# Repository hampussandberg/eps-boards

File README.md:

# ESP boards
Various ESP8266 and ESP32 boards

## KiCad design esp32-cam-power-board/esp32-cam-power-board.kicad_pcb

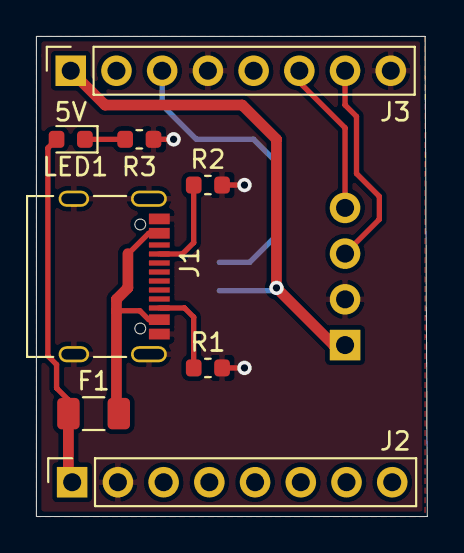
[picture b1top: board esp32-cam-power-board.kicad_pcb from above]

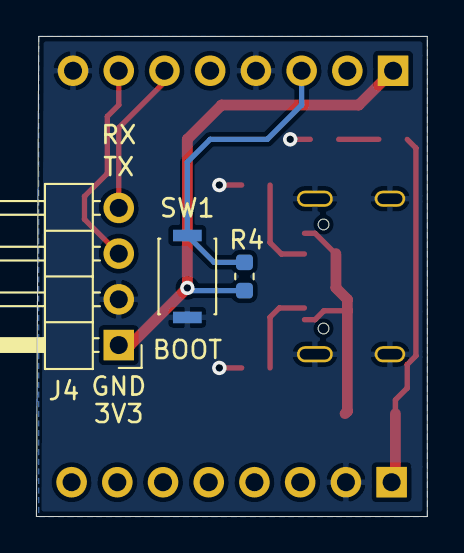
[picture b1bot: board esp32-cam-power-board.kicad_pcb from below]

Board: 2 copper layers, 21.7 x 26.7 mm, 11 parts (3 on the bottom side), 10 nets.

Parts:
F1: 0ZCJ0100FF2E; Fuse_1206_3216Metric
J1: USB_C_Receptacle_USB2.0; USB_C_Receptacle_Palconn_UTC16-G
J2, J3: Conn_01x08_Female; PinSocket_1x08_P2.54mm_Vertical
J4: Conn_01x04_Male; PinHeader_1x04_P2.54mm_Horizontal
LED1: Green; LED_0603_1608Metric
R1, R2: 5k1; R_0603_1608Metric
R3: 4k7; R_0603_1608Metric
R4: 10k; R_0603_1608Metric
SW1: SW_Push; SW_SPST_4x3x2mm

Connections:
+3V3: J3.1, J4.1, R4.1
/CC1: J1.A5, R2.1
/CC2: J1.B5, R1.1
/PP_VUSB: F1.1, J2.1, LED1.2
/PP_VUSB_RAW: F1.2, J1.A4, J1.A9, J1.B4, J1.B9
/RX: J3.6, J4.4
/TX: J3.7, J4.3
/~BOOT~: J3.3, R4.2, SW1.2
GND: J1.A1, J1.A12, J1.B1, J1.B12, J1.S1, J2.2, J3.4, J3.8, J4.2, R1.2, R2.2, R3.2, SW1.1
unnamed: LED1.1, R3.1

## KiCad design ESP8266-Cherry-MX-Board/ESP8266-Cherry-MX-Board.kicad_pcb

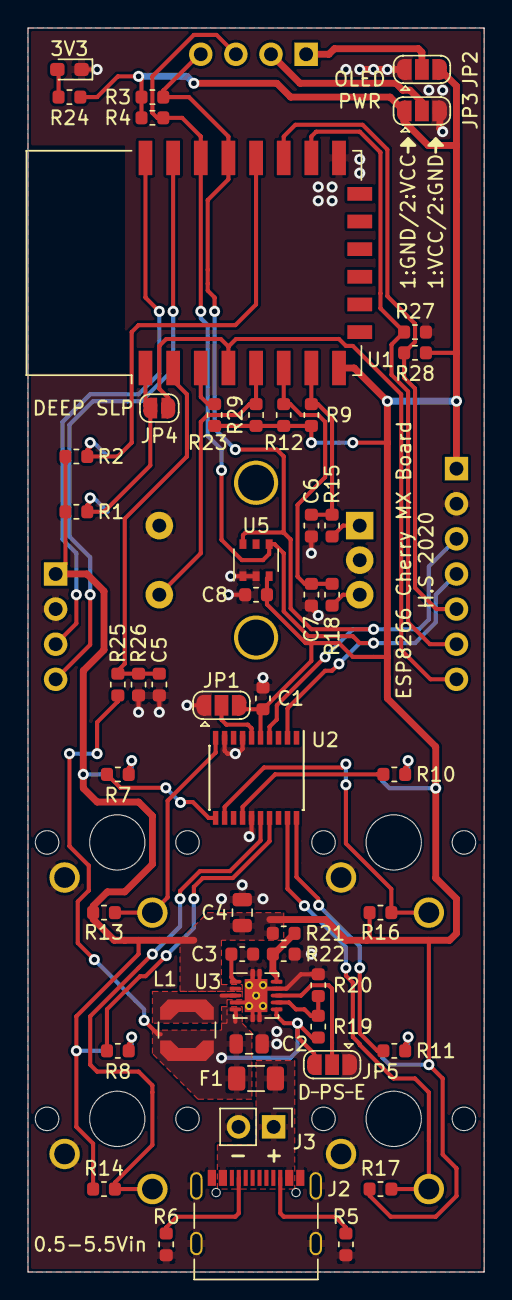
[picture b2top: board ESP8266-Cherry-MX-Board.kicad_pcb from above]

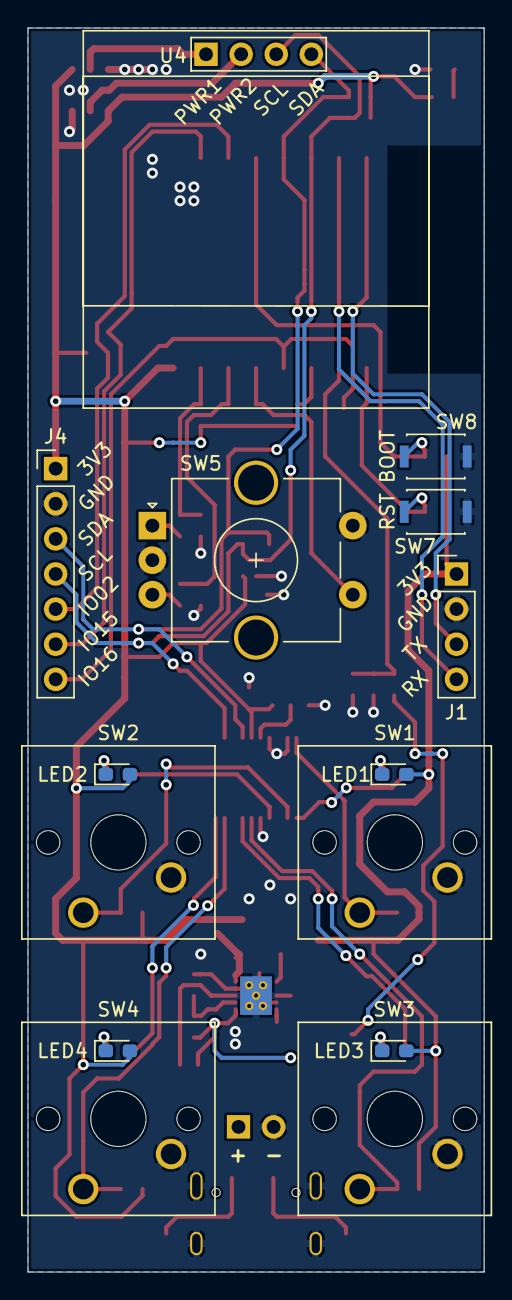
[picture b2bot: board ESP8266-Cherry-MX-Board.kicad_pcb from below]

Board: 2 copper layers, 33.0 x 90.0 mm, 65 parts (14 on the bottom side), 43 nets.

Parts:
3V3: Red; LED_0603_1608Metric_Pad1.05x0.95mm_HandSolder
C1, C3, C5, C8: 100n; C_0603_1608Metric
C2, C4: 10uF; C_0805_2012Metric
C6, C7: 10n; C_0603_1608Metric
F1: Polyfuse; Fuse_1206_3216Metric
J1: Conn_01x04_Male; PinHeader_1x04_P2.54mm_Vertical
J2: USB_C_Receptacle_USB2.0; USB_C_Receptacle_Palconn_UTC16-G
J3: Conn_01x02; PinHeader_1x02_P2.54mm_Vertical
J4: Conn_01x07_Male; PinHeader_1x07_P2.54mm_Vertical
JP1, JP2, JP3, JP5: SolderJumper_3_Open; SolderJumper-3_P1.3mm_Open_RoundedPad1.0x1.5mm
JP4: SolderJumper_2_Open; SolderJumper-2_P1.3mm_Open_RoundedPad1.0x1.5mm
L1: 2.2uH; L_Coilcraft_LPS4012
LED1, LED2, LED3, LED4: Blue; LED_0603_1608Metric_Pad1.05x0.95mm_HandSolder
R1, R2, R3, R4, R9, R12, R13, R14, R16, R17, R23, R24, R27, R28, R29: 10k; R_0603_1608Metric
R5, R6: 5.1k; R_0603_1608Metric
R7, R8, R10, R11: 330R; R_0603_1608Metric
R15, R18: 0R; R_0603_1608Metric
R19, R20, R22: 178k; R_0603_1608Metric
R21: 1M; R_0603_1608Metric
R25: 499k; R_0603_1608Metric
R26: 100k; R_0603_1608Metric
SW1, SW2, SW3, SW4: SW_SPST; SW_Cherry_MX_1.00u_PCB
SW5: PEC11L-4115F-S0020; RotaryEncoder_Alps_EC11E-Switch_Vertical_H20mm_CircularMoun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
SW7, SW8: SW_Push; SW_SPST_4x3x2mm
U1: ESP-12F; ESP-12E
U2: PCF8574; SSOP-20_4.4x6.5mm_P0.65mm
U3: TPS61200DRC; Texas_S-PVSON-N10_ThermalVias
U4: SSD1306; 128x64OLED
U5: PCT2075GVX‎; TSOP-6_1.65x3.05mm_P0.95mm

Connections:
+3V3: C1.2, C4.1, C8.2, J1.1, J4.1, JP1.3, JP2.3, JP3.1, LED1.2, LED2.2, LED3.2, LED4.2, R1.2, R2.2, R3.1, R4.1, R9.1, R12.1, R13.2, R14.2, R16.2, R17.2, R21.1, R23.1, R24.1, R28.1, R29.1, U1.8, U2.5, U3.2, U5.3
/ADC: C5.1, R25.1, R26.1, U1.2
/ENCODER_A: C6.1, R9.2, R15.1, U1.7
/ENCODER_B: C7.1, R12.2, R18.1, U1.6
/ENCODER_SW: R29.2, SW5.S1, U1.5
/GPIO0: R2.1, SW8.1, U1.18
/GPIO2: J4.5, R28.2, U1.17
/GPIO15: J4.6, R27.1, U1.16
/GPIO16: J4.7, JP4.2, U1.4
/I2C_SCL: J4.4, R4.2, U1.20, U2.2, U4.3, U5.4
/I2C_SDA: J4.3, R3.2, U1.19, U2.4, U4.4, U5.6
/LED_1: R7.1, U2.11
/LED_2: R10.1, U2.14
/LED_3: R8.1, U2.17
/LED_4: R11.1, U2.20
/RX: J1.4, U1.21
/SWITCH_1: R13.1, SW1.1, U2.10
/SWITCH_2: R16.1, SW2.1, U2.12
/SWITCH_3: R14.1, SW3.1, U2.16
/SWITCH_4: R17.1, SW4.1, U2.19
/TX: J1.3, U1.22
/~RST~: JP4.1, R1.1, SW7.2, U1.1
GND: 3V3.1, C1.1, C2.2, C3.2, C4.2, C5.2, C6.2, C7.2, C8.1, J1.2, J2.A1, J2.A12, J2.B1, J2.B12, J2.S1, J3.2, J4.2, JP1.1, JP2.1, JP3.3, JP5.1, R5.2, R6.2, R20.2, R22.2, R26.2, R27.2, SW1.2, SW2.2, SW3.2, SW4.2, SW5.C, SW5.S2, SW7.1, SW8.2, U1.15, U2.7, U2.9, U2.15, U3.4, U3.9, U3.11, U5.1, U5.2
unnamed: 3V3.2, R24.2
unnamed: C2.1, F1.1, JP5.3, L1.1, R19.1, R25.2, U3.5, U3.6
unnamed: C3.1, U3.1
unnamed: J2.A5, R6.1
unnamed: J2.B5, R5.1
unnamed: JP1.2, U2.6
unnamed: JP2.2, U4.1
unnamed: JP3.2, U4.2
unnamed: JP5.2, U3.8
unnamed: L1.2, U3.3
unnamed: LED1.1, R7.2
unnamed: LED2.1, R10.2
unnamed: LED3.1, R8.2
unnamed: LED4.1, R11.2
unnamed: R15.2, SW5.A
unnamed: R18.2, SW5.B
unnamed: R19.2, R20.1, U3.7
unnamed: R21.2, R22.1, U3.10
unnamed: R23.2, U1.3
VBUS: F1.2, J2.A4, J2.A9, J2.B4, J2.B9, J3.1

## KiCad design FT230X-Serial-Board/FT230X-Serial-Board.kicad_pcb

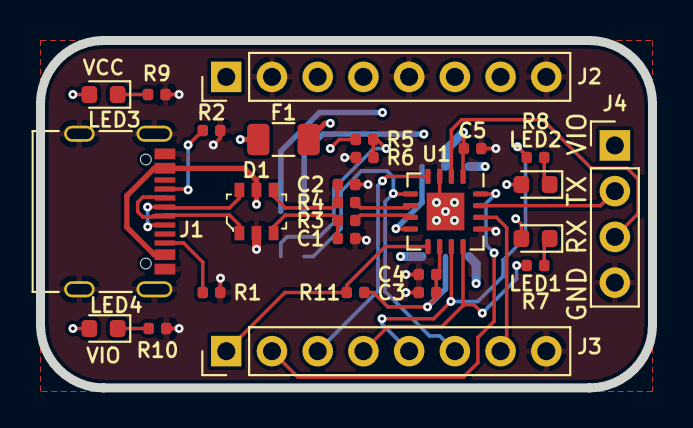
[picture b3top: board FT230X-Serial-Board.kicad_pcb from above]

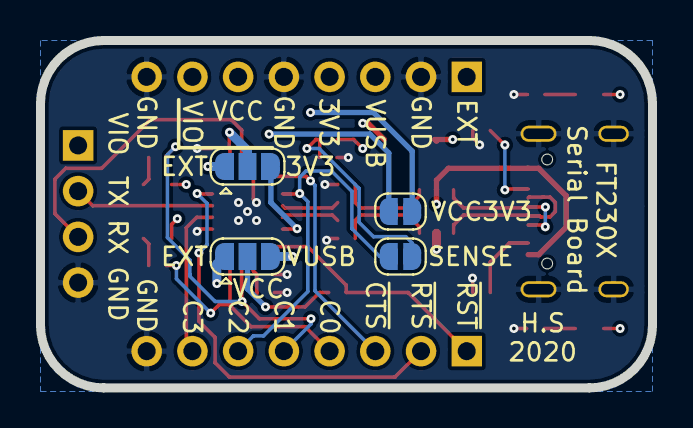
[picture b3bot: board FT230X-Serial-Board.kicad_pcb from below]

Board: 4 copper layers, 34.0 x 19.3 mm, 31 parts (4 on the bottom side), 29 nets.

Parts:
C1, C2: 47pF; C_0402_1005Metric
C3: 4u7; C_0402_1005Metric
C4, C5: 100n; C_0402_1005Metric
D1: IP4234CZ6; SC-74
F1: 0ZCJ0100FF2E; Fuse_1206_3216Metric
J1: USB_C_Receptacle_USB2.0; USB_C_Receptacle_Palconn_UTC16-G
J2, J3: Conn_01x08_Male; PinHeader_1x08_P2.54mm_Vertical
J4: Conn_01x04_Male; PinHeader_1x04_P2.54mm_Vertical
JP1, JP3: Jumper_3_Open; SolderJumper-3_P1.3mm_Open_RoundedPad1.0x1.5mm
JP2, JP4: Jumper_2_Open; SolderJumper-2_P1.3mm_Open_RoundedPad1.0x1.5mm
LED1: Red; LED_0603_1608Metric
LED2, LED3, LED4: Green; LED_0603_1608Metric
R1, R2: 5k1; R_0402_1005Metric
R3, R4: 27; R_0402_1005Metric
R5, R9, R10: 4k7; R_0402_1005Metric
R6: 10k; R_0402_1005Metric
R7, R8: 270; R_0402_1005Metric
R11: nc; R_0402_1005Metric
U1: FT230XQ; QFN-16-1EP_4x4mm_P0.65mm_EP2.1x2.1mm

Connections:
/CBUS0: J3.4, R7.2, U1.12
/CBUS1: J3.5, R8.2, U1.11
/CBUS2: J3.6, JP2.2, U1.5
/CBUS3: J3.7, U1.14
/CC1: J1.A5, R2.1
/CC2: J1.B5, R1.1
/PP3V3OUT: J2.4, JP3.3, JP4.2, U1.8
/PPEXT: J2.1, JP1.1, JP3.1
/PPIO: C5.2, J2.7, J4.1, JP3.2, LED1.2, LED2.2, LED4.2, U1.1
/PPVCC: C3.1, C4.2, J2.6, JP1.2, JP4.1, LED3.2, R11.1, U1.10
/PP_VUSB: F1.1, J2.3, JP1.3, R5.1
/PP_VUSB_RAW: D1.5, F1.2, J1.A4, J1.A9, J1.B4, J1.B9
/RESET_N: J3.1, R11.2, U1.9
/UART_RX: J4.3, U1.2
/UART_TX: J4.2, U1.15
/UART_~CTS: J3.3, U1.4
/UART_~RTS: J3.2, U1.16
/USBDR_N: R3.2, U1.7
/USBDR_P: R4.2, U1.6
/USB_D_N: C1.2, D1.3, R3.1
/USB_D_P: C2.2, D1.4, R4.1
/USB_D_RAW_N: D1.1, J1.A7, J1.B7
/USB_D_RAW_P: D1.6, J1.A6, J1.B6
/VUSB_SENSE: JP2.1, R5.2, R6.1
GND: C1.1, C2.1, C3.2, C4.1, C5.1, D1.2, J1.A1, J1.A12, J1.B1, J1.B12, J1.S1, J2.2, J2.5, J2.8, J3.8, J4.4, R1.2, R2.2, R6.2, R9.2, R10.2, U1.3, U1.13, U1.17
unnamed: LED1.1, R7.1
unnamed: LED2.1, R8.1
unnamed: LED3.1, R9.1
unnamed: LED4.1, R10.1

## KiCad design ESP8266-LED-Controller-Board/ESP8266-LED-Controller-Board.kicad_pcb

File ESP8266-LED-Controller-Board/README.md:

# ESP8266-LED-Controller-Board
- [GitHub repository <i class="fa fa-external-link"></i>](https://github.com/hampussandberg/esp-boards/tree/master/ESP8266-LED-Controller-Board)
- [Interactive BOM](ESP8266-LED-Controller-Board-ibom.html){target="\_blank"}

Interactive BOM created using: https://github.com/openscopeproject/InteractiveHtmlBom

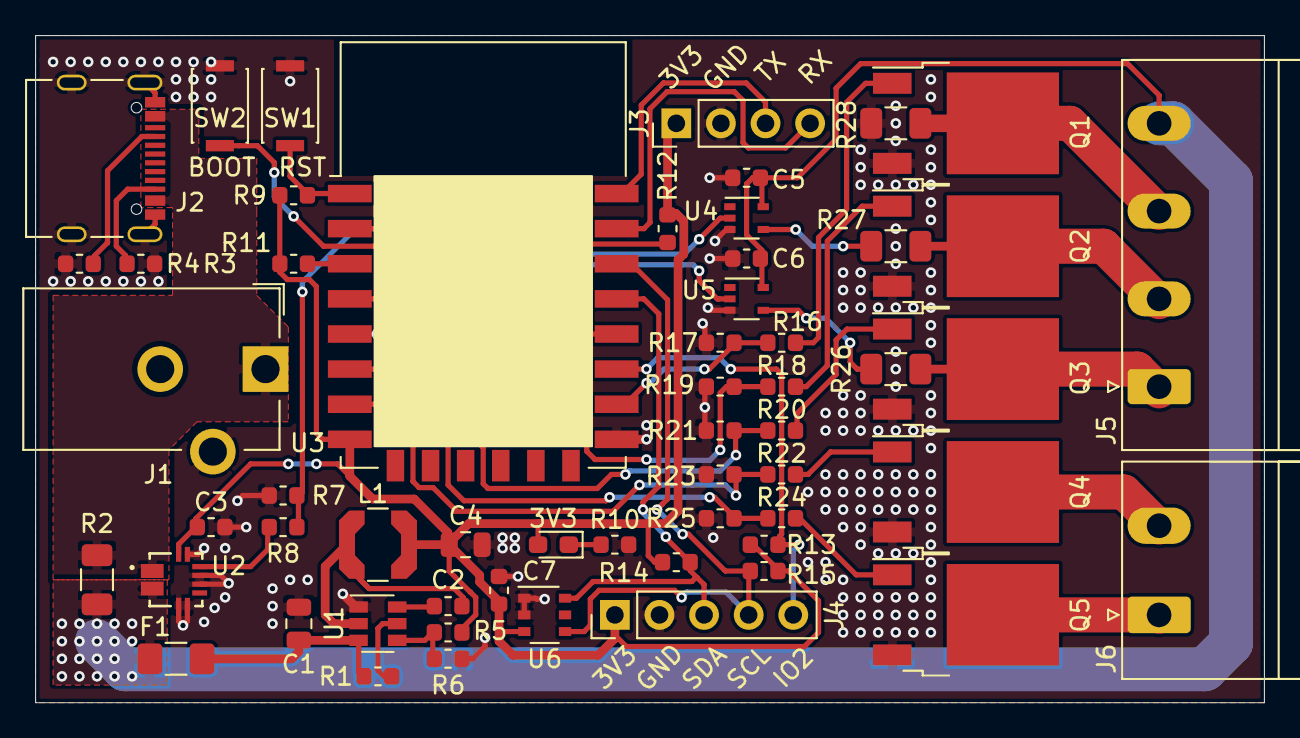
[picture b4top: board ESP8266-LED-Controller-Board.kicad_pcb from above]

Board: 2 copper layers, 70.0 x 38.0 mm, 57 parts (0 on the bottom side), 39 nets.

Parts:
3V3: RED; LED_0603_1608Metric_Pad1.05x0.95mm_HandSolder
C1, C4: 22u; C_0805_2012Metric
C2, C3, C5, C6, C7: 100n; C_0603_1608Metric
F1: 0ZCJ0050AF2E; Fuse_0ZCJ_1206
J1: Barrel_Jack_Switch; BarrelJack_CUI_PJ-102AH_Horizontal
J2: USB_C_Receptacle_USB2.0; USB_C_Receptacle_Palconn_UTC16-G
J3: Conn_01x04_Male; PinHeader_1x04_P2.54mm_Vertical
J4: Conn_01x05_Male; PinHeader_1x05_P2.54mm_Vertical
J5: Screw_Terminal_01x04; PhoenixContact_MSTBA_2,5_4-G_1x04_P5.00mm_Horizontal
J6: Screw_Terminal_01x02; PhoenixContact_MSTBA_2,5_2-G-5,08_1x02_P5.08mm_Horizontal
L1: 2.2uH; L_Coilcraft_LPS4012
Q1, Q2, Q3, Q4, Q5: NTD5867NLT4G; TO-252-2
R1, R6, R7, R9, R10, R11, R12, R13, R14, R15, R17, R19, R21, R23, R25: 10k; R_0603_1608Metric
R2, R26, R27, R28: 0R; R_1206_3216Metric
R3, R4: 5k1; R_0603_1608Metric
R5: 33k2; R_0603_1608Metric
R8: 22k; R_0603_1608Metric
R16, R18, R20, R22, R24: 100R; R_0603_1608Metric
SW1, SW2: SW_Push; SW_SPST_4x3x2mm
U1: TPS563200; SOT-23-6
U2: ACS70331EESATR-005U3; ALLEGRO_ACS70331EESATR-005U3
U3: ESP-12F; ESP-12E
U4, U5: SN74LV1T34DCKR; SOT-353_SC-70-5
U6: PCT2075GVX‎; TSOP-6_1.65x3.05mm_P0.95mm

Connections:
+3V3: 3V3.2, C3.1, C4.1, C7.2, J3.1, J4.1, L1.2, R5.1, R9.1, R11.1, R12.2, R13.1, R14.1, R15.1, U2.12, U3.8, U6.3
/BOOT: R12.1, SW2.1, U3.18
/GPIO2: J4.5, R13.2, U3.17
/I2C_SCL: J4.4, R15.2, U3.20, U6.4
/I2C_SDA: J4.3, R14.2, U3.19, U6.6
/I_MEASURE: R8.2, U2.10
/LED_B_OUT: J5.1, Q3.2, R26.2
/LED_CW_CTRL: R24.2, R25.2, U3.4
/LED_CW_OUT: J6.1, Q5.2
/LED_G_OUT: J5.2, Q2.2, R27.2
/LED_R_CTRL: R16.2, R17.2, U3.16
/LED_R_OUT: J5.3, Q1.2, R28.2
/LED_WW_CTRL: R22.2, R23.2, U3.6
/LED_WW_OUT: J6.2, Q4.2
/PIXEL_CLK_3V3-LED_B_CTRL: R20.2, R21.2, U3.5, U5.2
/PIXEL_CLK_5V: R26.1, U5.4
/PIXEL_DATA_3V3-LED_G_CTRL: R18.2, R19.2, U3.7, U4.2
/PIXEL_DATA_5V: R27.1, U4.4
/RX: J3.4, U3.21
/TX: J3.3, U3.22
/~RST~: R9.2, SW1.2, U3.1
GND: C1.2, C3.2, C4.2, C5.2, C6.2, C7.1, J1.2, J1.3, J2.A1, J2.A12, J2.B1, J2.B12, J2.S1, J3.2, J4.2, Q1.3, Q2.3, Q3.3, Q4.3, Q5.3, R3.2, R4.2, R6.2, R7.2, R10.2, R17.1, R19.1, R21.1, R23.1, R25.1, R28.1, SW1.1, SW2.2, U1.1, U2.5, U2.6, U2.8, U2.9, U2.11, U3.15, U4.3, U5.3, U6.1, U6.2
unnamed: 3V3.1, R10.1
unnamed: C1.1, F1.2, R1.2, U1.3
unnamed: C2.1, L1.1, U1.2
unnamed: C2.2, U1.6
unnamed: J2.A5, R4.1
unnamed: J2.B5, R3.1
unnamed: Q1.1, R16.1
unnamed: Q2.1, R18.1
unnamed: Q3.1, R20.1
unnamed: Q4.1, R22.1
unnamed: Q5.1, R24.1
unnamed: R1.1, U1.5
unnamed: R5.2, R6.1, U1.4
unnamed: R7.1, R8.1, U3.2
unnamed: R11.2, U3.3
VDD: C5.1, C6.1, F1.1, J5.4, R2.2, U2.3, U2.4, U4.5, U5.5
VIN: J1.1, J2.A4, J2.A9, J2.B4, J2.B9, R2.1, U2.1, U2.2

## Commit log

2020-02-15 Added ESP8266-LED-Controller-Board
2020-02-15 Added interactive BOM.
2020-02-16 Cleanup and exported STEP.
2020-02-16 Fixed comment.
2020-02-16 Added missing voltage divider for adc.
2020-02-16 Updated 3d renderings.
2020-02-16 Added pullup to EN pin just in case.
2020-02-16 Added silkscreen under esp module for protection against shorts.
2020-02-16 Fixed tilted silkscreen...
2020-02-16 Updated readme and part number.
2020-03-08 Fixed errors in version 1 of the board.
2020-03-11 Fixed wrong footprint.
2020-03-11 Fixed wrong designator on LED.
2020-03-12 Changed buffers to SN74LV1T34DCKR because the previous SN74LVC2G17DCKR do not work well with 3.3V logic when VCC is 5V. Changed passive footprints to non-handsolder version.
2020-03-12 Added temperature sensors.
2020-03-18 Updated for manufacturing.
2020-03-26 Updated 3D reference.
2020-03-30 Updated gitignore.
2020-03-30 Added ESP8266-Cherry-MX-Board
2020-03-30 Added README
2020-03-30 Cleanup of schematic and silkscreen.
2020-03-31 Updated ESP8266-Cherry-MX-Board resources.
2020-06-13 Added FT230X-Serial-Board.
2020-06-13 Renamed.
2020-06-13 Cleanup of silkscreen.
2020-07-03 Fixed errors on ESP8266-Cherry-MX-Board.
2020-07-03 Fixed errors on FT230X-Serial-Board.
2020-07-04 Updated component values.
2020-10-10 Added esp32-cam-power-board.
2020-10-21 Added README.
